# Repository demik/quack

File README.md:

# Quack Mouse Converter   [![Badge License]][License]&nbsp;[![Badge CI]][CI]

A dongle that allows various retro systems to use the `Apple Desktop Bus` as well as `Bluetooth 2+` mice through their `quadrature` mouse ports.

<br>
<br>
<br>

<div align = center>

[![Button Documentation]][Documentation]   
[![Button Firmware]][Firmware]   
[![Button PCB]][PCB]   
[![Button Changelog]][Changelog]

<br>
<br>

</div>

<br>
<br>

## Supported

#### Systems

<kbd>&nbsp;&nbsp;Macintosh 128 / 512 / Plus&nbsp;&nbsp;</kbd> 
<kbd>&nbsp;&nbsp;Apple Lisa&nbsp;&nbsp;</kbd> 
<kbd>&nbsp;&nbsp;Apple IIc&nbsp;&nbsp;</kbd> 
<a href="https://github.com/DosFox1/OSHintosh"><kbd>&nbsp;&nbsp;OSHintosh&nbsp;&nbsp;</kbd></a>

#### Connection Types

<kbd>  Apple Desktop Bus  </kbd> <kbd>  Bluetooth Classic 2+  </kbd>

<br>
<br>

<!----------------------------------------------------------------------------->

[Documentation]: https://github.com/demik/quack/wiki

[Changelog]: ChangeLog.md
[Firmware]: main/README.md
[License]: LICENSE
[PCB]: EDA/ChangeLog.md
[CI]: https://github.com/demik/quack/actions/workflows/idf.yml
[OSHintosh]: https://github.com/DosFox1/OSHintosh

<!-------------------------------[ Badges ]----------------------------------->

[Badge License]: https://img.shields.io/badge/License-Apache_2.0-961b1f?labelColor=D22128
[Badge CI]: https://github.com/demik/quack/actions/workflows/idf.yml/badge.svg?branch=master&event=push

<!-------------------------------[ Buttons ]----------------------------------->

[Button Documentation]: https://img.shields.io/badge/Documentation-0099E5?style=for-the-badge&logoColor=white&logo=BookStack
[Button Changelog]: https://img.shields.io/badge/Changelog-21375A?style=for-the-badge&logoColor=white&logo=AzureArtifacts
[Button Firmware]: https://img.shields.io/badge/Firmware-E5426E?style=for-the-badge&logoColor=white&logo=ROS
[Button PCB]: https://img.shields.io/badge/PCB-007c40?style=for-the-badge&logoColor=white&logo=PowerApps

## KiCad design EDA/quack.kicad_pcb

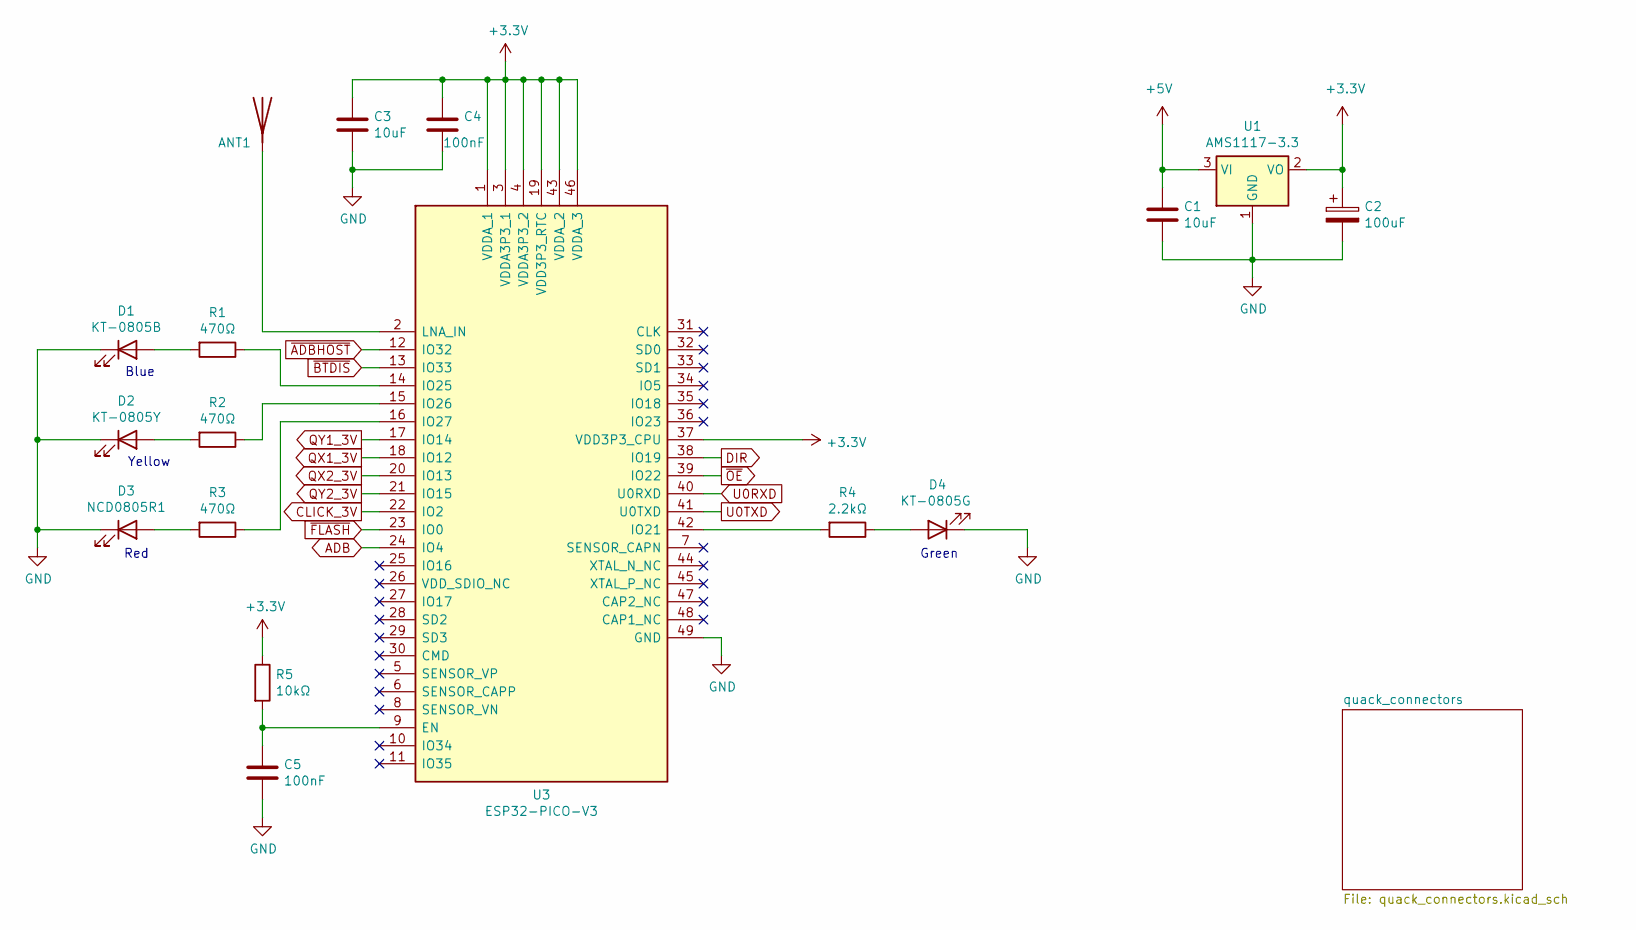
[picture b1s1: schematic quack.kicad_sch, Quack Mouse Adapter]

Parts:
ANT1: Antenna_Shield; Texas_SWRA117D_2.4GHz_Right
C1, C3: 10uF; C_0805_2012Metric
C2: 100uF; CP_EIA-3528-12_Kemet-T
C4, C5: 100nF; C_0805_2012Metric
D1: KT-0805B; LED_0805_2012Metric
D2: KT-0805Y; LED_0805_2012Metric
D3: NCD0805R1; LED_0805_2012Metric
D4: KT-0805G; LED_0805_2012Metric
R1, R2, R3: 470Ω; R_0805_2012Metric
R4: 2.2kΩ; R_0805_2012Metric
R5: 10kΩ; R_0805_2012Metric
U1: AMS1117-3.3; SOT-223-3_TabPin2
U3: ESP32-PICO-V3; QFN-48-1EP_7x7mm_P0.5mm_EP5.3x5.3mm; Mouser Part Number 356-ESP32-PICO-V3

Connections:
+3.3V: C2.1, C3.1, C4.1, R5.1, U1.2 (VO), U3.1 (VDDA_1), U3.3 (VDDA3P3_1), U3.4 (VDDA3P3_2), U3.19 (VDD3P3_RTC), U3.37 (VDD3P3_CPU), U3.43 (VDDA_2), U3.46 (VDDA_3); also elsewhere on the board
+5V: C1.1, U1.3 (VI); also elsewhere on the board
ADB: U3.24 (IO4); also elsewhere on the board
CLICK_3V: U3.22 (IO2); also elsewhere on the board
DIR: U3.38 (IO19); also elsewhere on the board
GND: C1.2, C2.2, C3.2, C4.2, C5.2, D1.1 (K), D2.1 (K), D3.1 (K), D4.1 (K), U1.1 (GND), U3.49 (GND); also elsewhere on the board
unnamed: ANT1.1 (A), U3.2 (LNA_IN)
unnamed: D1.2 (A), R1.2
unnamed: D2.2 (A), R2.2
unnamed: D3.2 (A), R3.2
unnamed: D4.2 (A), R4.1
unnamed: C5.1, R5.2, U3.9 (EN)
unnamed: R4.2, U3.42 (IO21)
unnamed: R1.1, U3.14 (IO25)
unnamed: R2.1, U3.15 (IO26)
unnamed: R3.1, U3.16 (IO27)
QX1_3V: U3.18 (IO12); also elsewhere on the board
QX2_3V: U3.20 (IO13); also elsewhere on the board
QY1_3V: U3.17 (IO14); also elsewhere on the board
QY2_3V: U3.21 (IO15); also elsewhere on the board
U0RXD: U3.40 (U0RXD); also elsewhere on the board
U0TXD: U3.41 (U0TXD); also elsewhere on the board
~ADBHOST: U3.12 (IO32); also elsewhere on the board
~BTDIS: U3.13 (IO33); also elsewhere on the board
~FLASH: U3.23 (IO0); also elsewhere on the board
~OE: U3.39 (IO22); also elsewhere on the board

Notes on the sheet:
Blue
Red
Green
Yellow

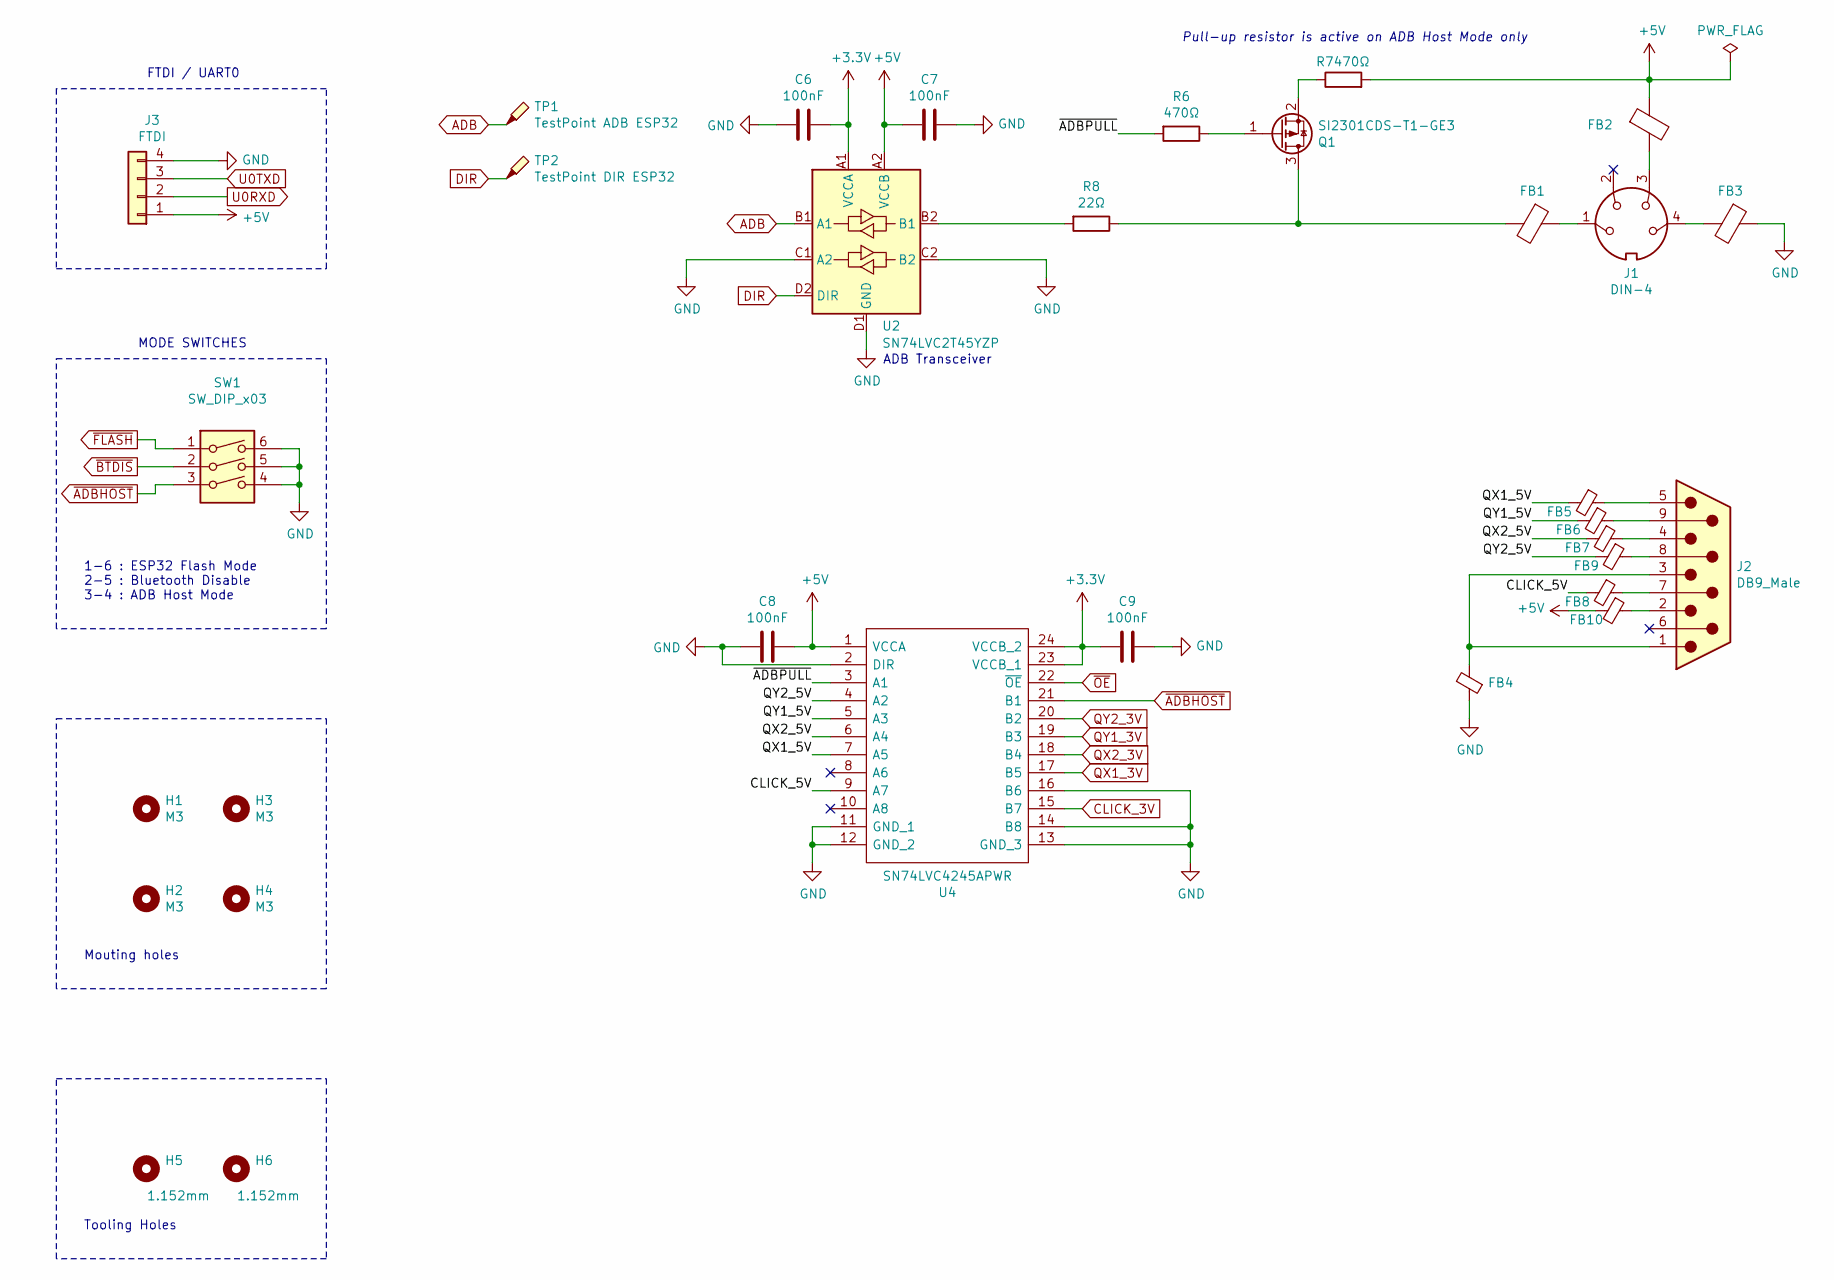
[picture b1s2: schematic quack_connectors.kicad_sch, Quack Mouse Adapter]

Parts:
C6, C7, C8, C9: 100nF; C_0805_2012Metric
FB1, FB2, FB3, FB4, FB5, FB6, FB7, FB8, FB9, FB10: GZ2012D601TF; L_0805_2012Metric
H1, H2, H3, H4: M3; MountingHole_3.2mm_M3_Pad
H5, H6: 1.152mm; MountingHole_1.152mm
J1: DIN-4; 5749181-1
J2: DB9_Male; 23018431
J3: FTDI; PinHeader_1x04_P2.54mm_Vertical
Q1: SI2301CDS-T1-GE3; SOT-23
R6, R7: 470Ω; R_0805_2012Metric
R8: 22Ω; R_0805_2012Metric
SW1: SW_DIP_x03; SW_DIP_SPSTx03_Slide_9.78x9.8mm_W7.62mm_P2.54mm
TP1: TestPoint ADB ESP32; TestPoint_Pad_1.0x1.0mm
TP2: TestPoint DIR ESP32; TestPoint_Pad_1.0x1.0mm
U2: SN74LVC2T45YZP; Texas_DSBGA-8_0.9x1.9mm_Layout2x4_P0.5mm
U4: SN74LVC4245APWR; TSSOP-24_4.4x7.8mm_P0.65mm; Mouser Part Number 595-SN74LVC4245APWR

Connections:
+3.3V: C6.1, C9.2, U2.A1 (VCCA), U4.23 (VCCB_1), U4.24 (VCCB_2); also elsewhere on the board
+5V: C7.2, C8.1, FB2.1, FB10.2, J3.1, R7.2, U2.A2 (VCCB), U4.1 (VCCA); also elsewhere on the board
/quack_connectors/CLICK_5V: FB8.2, U4.9 (A7)
/quack_connectors/QX1_5V: FB5.2, U4.7 (A5)
/quack_connectors/QX2_5V: FB7.2, U4.6 (A4)
/quack_connectors/QY1_5V: FB6.2, U4.5 (A3)
/quack_connectors/QY2_5V: FB9.2, U4.4 (A2)
/quack_connectors/~ADBPULL: R6.2, U4.3 (A1)
ADB: TP1.1, U2.B1 (A1); also elsewhere on the board
CLICK_3V: U4.15 (B7); also elsewhere on the board
DIR: TP2.1, U2.D2 (DIR); also elsewhere on the board
GND: C6.2, C7.1, C8.2, C9.1, FB3.1, FB4.1, J3.4, SW1.4, SW1.5, SW1.6, U2.C1 (A2), U2.C2 (B2), U2.D1 (GND), U4.2 (DIR), U4.11 (GND_1), U4.12 (GND_2), U4.13 (GND_3), U4.14 (B8), U4.16 (B6); also elsewhere on the board
unnamed: FB1.1, J1.1
unnamed: FB2.2, J1.3
unnamed: FB3.2, J1.4
unnamed: FB4.2, J2.1, J2.3
unnamed: FB5.1, J2.5
unnamed: FB6.1, J2.9
unnamed: FB7.1, J2.4
unnamed: FB8.1, J2.7
unnamed: FB9.1, J2.8
unnamed: FB10.1, J2.2
unnamed: FB1.2, Q1.3 (D), R8.1
unnamed: Q1.1 (G), R6.1
unnamed: Q1.2 (S), R7.1
unnamed: R8.2, U2.B2 (B1)
QX1_3V: U4.17 (B5); also elsewhere on the board
QX2_3V: U4.18 (B4); also elsewhere on the board
QY1_3V: U4.19 (B3); also elsewhere on the board
QY2_3V: U4.20 (B2); also elsewhere on the board
U0RXD: J3.2; also elsewhere on the board
U0TXD: J3.3; also elsewhere on the board
~ADBHOST: SW1.3, U4.21 (B1); also elsewhere on the board
~BTDIS: SW1.2; also elsewhere on the board
~FLASH: SW1.1; also elsewhere on the board
~OE: U4.22 (~OE); also elsewhere on the board

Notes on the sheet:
1-6 : ESP32 Flash Mode 2-5 : Bluetooth Disable 3-4 : ADB Host Mode
Mouting holes
MODE SWITCHES
ADB Transceiver
Pull-up resistor is active on ADB Host Mode only
Tooling Holes
FTDI / UART0

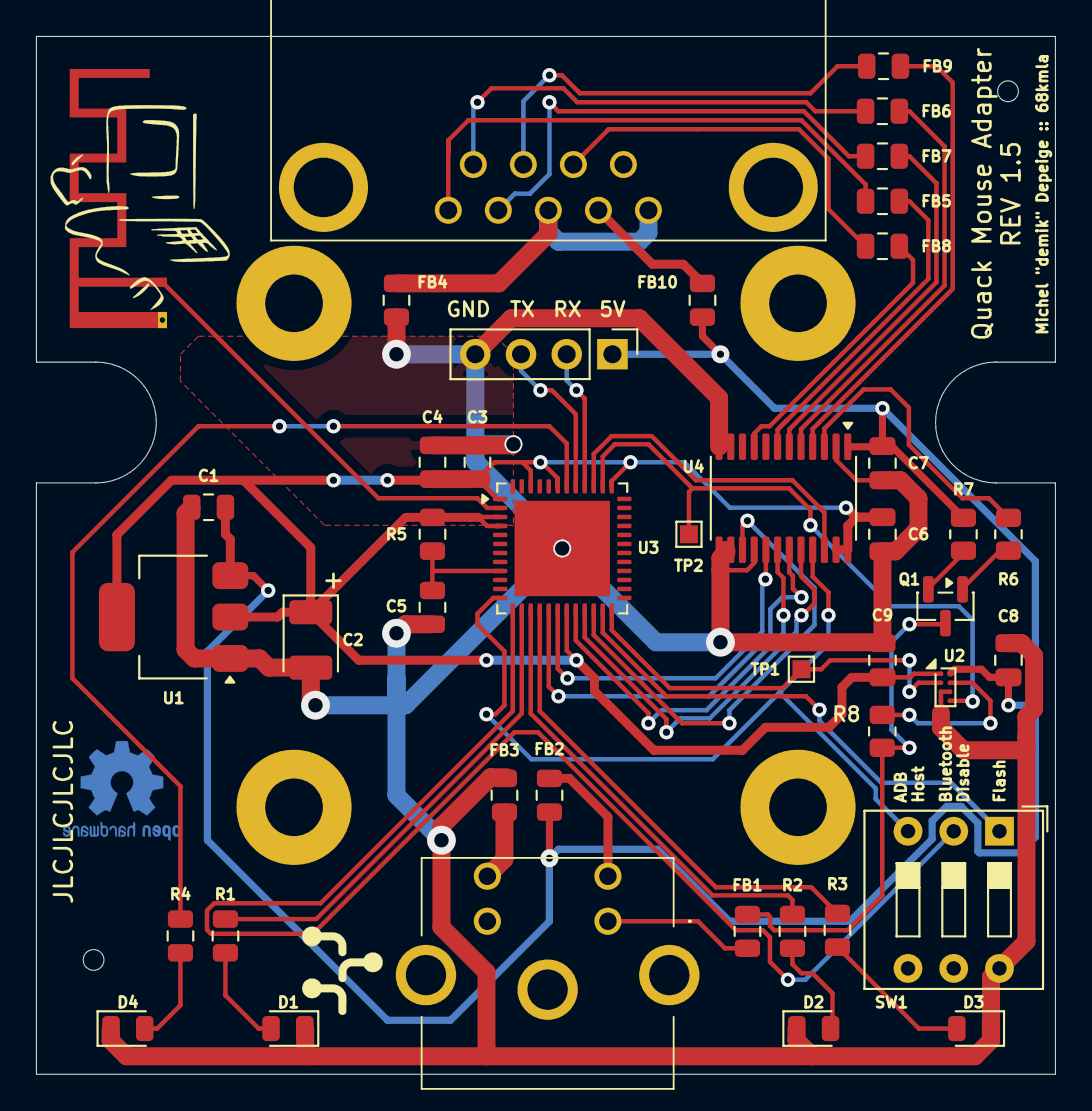
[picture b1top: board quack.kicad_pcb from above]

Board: 2 copper layers, 56.6 x 57.7 mm, 49 parts (0 on the bottom side), 46 nets.

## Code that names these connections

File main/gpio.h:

/*
 *  gpio.h
 *  quack
 *
 *  Created by Michel DEPEIGE on 13/09/2020.
 *  Copyright (c) 2020 Michel DEPEIGE.
 *
 * This program is free software; you can redistribute it and/or modify
 * it under the terms of the Apache License, Version 2.0 (the "License");
 * You may obtain a copy of the License at:
 *
 *      http://www.apache.org/licenses/LICENSE-2.0
 *
 * Unless required by applicable law or agreed to in writing, software
 * distributed under the License is distributed on an "AS IS" BASIS,
 * WITHOUT WARRANTIES OR CONDITIONS OF ANY KIND, either express or implied.
 * See the License for the specific language governing permissions and
 * limitations under the License.
 *
 */

#ifndef GPIO_H
#define GPIO_H

/* prototypes */
void	gpio_init(void);
void    gpio_transceiver_disable(void);
void    gpio_transceiver_enable(void);

/* GPIO pins definitions
 *
 * pin layout is compatible with ESP32-CAM module for prototyping
 * LEDs aren't avaible on ESP32-CAM but DEBUG LED (Camera connector)
 *
 * on ESP32-CAM the following pins are already used:
 * - CSI_MCLK (GPIO0)
 * - U0TXD (GPIO1)
 * - U0TXD (GPIO3)
 * - FLASH (GPIO4)
 *
 * on ESP32-PICO-D4, the following pins are used for connecting the
 * embedded flash:
 * - CLK (GPIO6)
 * - SD0 (GPIO7)
 * - SD1 (GPIO8)
 * - CMD (GPIO11)
 * - GPIO16
 * - GPIO17
 */

#define GPIO_ADB		4
#define GPIO_CLICK		2
#define GPIO_QX1		12
#define GPIO_QX2		13
#define GPIO_QY1		14
#define GPIO_QY2		15

#define GPIO_DIR		19
#define GPIO_OE		22
#define GPIO_ADBSRC		32
#define GPIO_BTOFF		33

#define GPIO_GREENLED	21
#define GPIO_BLUELED	25
#define GPIO_YELLOWLED	26
#define GPIO_REDLED		27

#define GPIO_NULL		5

#endif

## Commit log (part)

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2020-09-15 added pin usage text + logos
2020-09-15 moved libs to subfolder
2020-09-25 added beads to reduce EMI
2020-12-14 upgraded toolkit to v4.2@20201214
2020-12-14 starting to work with LEDs
2020-12-16 added led management tasks
2020-12-18 some bluetooth code cleaning
2020-12-18 board revision 1.1
2020-12-21 added missing GPIO + disable Bluetooth if /BTOFF
2020-12-30 bluetooth tinkering
2020-12-30 revision 1.2: move ADB socket 2mm out
2020-12-31 fixed indenting
2021-01-08 try to init adb
2021-01-08 Board revision 1.2
2021-01-11 init ADB devices correctly
2021-03-21 start of ADB stack: send reset command on startup
2021-03-22 more adb coding + ESP-IDF update
2021-03-23 added missing adb.h
2021-03-24 Update ChangeLog.md
    Formating fixes
2021-03-24 adb clode cleaning
2021-04-01 more ADB hakinck
2021-04-03 replaced RXS0108EPWR by 74LVC2T45 + 74LVC4245
2021-04-03 mix fixes: silk, routing, 3D shapes
2021-04-04 fixed quad transceiver footprint + reduce led brightness
2021-04-05 PCB version 1.3
2021-04-05 fixed some SMT positions for pick and place
2021-04-17 added mounting holes to schematic
2021-04-18 Pull request #6385 from ESP-IDF
2021-04-18 tuned sdkconfig to get Bluetooth working again
2021-04-20 Quadrature and Bluetooth tinkering
2021-05-03 ADB Parsing 90% done, quadrature output issues
2021-05-07 SDK v4.2.1 update
2021-05-07 Changed pin code to 0000
2021-05-08 ADB code cleaning
2021-05-08 increase tick rate to 250Hz
2021-05-08 fixed timings and code cleaning
2021-05-08 Quadratures fixes: x movement, pullups, timings
2021-05-09 added ADB Mouse HotPlug management
2021-05-09 bluetooth -> quadrature 90% working. Need to tweak timings
2021-05-31 fixed ADB Sync timing
2021-06-08 PCB v1.4
2021-06-10 License project with Apache version 2.0
2021-08-05 increase RMT buffer and stability on data rx errors
2021-08-05 code compilation optimizations
2021-08-09 hardened the ADB Host to spurious transmissions a little bit
2021-08-09 code cleaning
2021-08-11 renamed ADB mouse mode to ADB idle mode
2021-08-15 fixed R1 and R4 values
2021-08-16 rotated U2 by 90°
2021-08-16 moved LEDs to LEDC module, fade slow blink, and move LEDs to CPU 1
2021-08-17 commited SDK 4.2 patch
2021-08-18 rename Bluetooth Host function as blue_h_*
2021-08-18 Licenses update + basic ADB to Bluetooth
2021-08-20 switched auth to ESP_IO_CAP_OUT
2021-08-20 do not send mouse updated to BLE if not connected
2021-08-21 code cleaning + freeing memory after init
2021-08-21 move quadrature tasks from notification to queue
2021-08-22 pin LED and ADB to core 1 again
2021-08-22 Firmware ChangeLog created
2021-08-23 Updating main README.md
2021-08-24 Added Wiki link
2021-08-24 Documentation for main subfolder
2021-08-26 Fixed wording
2021-09-08 Datasheet for ADB Socket
2021-09-19 compile against SDK v4.2.2
2021-09-20 fixed BT LED state when using multiple mouses
2021-10-12 added PCB image
2021-10-12 Added photo on README.md
2021-10-30 added support for MicroSpeed MacTRAC 2.0
2021-10-30 fixed BT LED state in case some mouse is reconnecting while the quack is scanning
2021-11-20 Added support for Apple Lisa
2021-12-02 provides some slight acceleration and desceleration on bluetooth mouses
2021-12-22 fix typo
2021-12-23 Reworked README
2021-12-23 Fixed Names
2022-01-04 added back panel using a PCB
2022-01-04 cleaning
2022-04-03 Upgraded SDK to v4.2.3
2022-07-05 Cut Out Preview
2022-07-05 Formatted README
2022-07-05 Adjusted Spacing
2022-07-05 Updated Support Section
2022-08-02 Adjusted Badge Style
2022-08-03 Added Bigger Preview
2023-12-28 Upgraded SDK to v5.1.2
2023-12-28 Updated ChangeLog to 1.4.5
2024-06-03 early work to restore ADB to bluetooth functionality
2024-06-04 added support for Kensington ADB Devices
2024-06-05 fix ADB start and stop bit timings
2024-06-06 Upgraded SDK to v5.2.2
2024-06-07 added complex PCB front panel
2024-06-08 New FR-4 based front panel with shine-through LEDs
2024-06-17 sync register probing to scheduling
2024-06-17 added new FR-4 front panel
2024-06-18 added half click feature (on BT right click)
2024-06-25 added support for MacAlly Joystick (thanks tashtari@68kmla !)
2024-07-02 added Apple IIc compatibility
2024-08-10 esp_hidh_dev_open() doesn't give a toss about BLE address types in our case
2024-08-14 added wii remote support (buttons)
2024-08-15 updated README for v1.4.8
2024-08-22 added basic support for some PDP Rock Candy Wiimotes
2024-08-29 added resources for esp_8_bit build
2024-08-29 added README for Quack X esp_8_bit
2024-08-29 fixed typo
2024-09-25 Back panel update: Apple IIc
2024-09-25 modified clearance
2025-02-10 upgraded Changelog for v1.4.9
2025-03-03 Create idf.yml
    gibve a try at espressif/esp-idf-ci-action
2025-03-03 only start github actions when push to master/main
2025-03-03 ESP-IDF v5.4 code modifications
2025-03-03 fix GHA path
2025-03-03 5.4.0 doc update
2025-03-03 added Mighty Mouse driver
2025-03-03 Update README.md
    added CI badge + minot fixes
2025-03-07 upgraded Changelog for v1.4.10
2025-03-08 added name to action idf.yml
2025-03-18 added flash switch watchdog
2025-03-20 Revert "added flash switch watchdog"
    This reverts commit 9152b953aa4b516238fd8f009775ccb52d42a4be because you can't enter bootloader from esp_restart() on ESP32
2025-06-29 1.4.11 update
2025-06-29 provisioned m5769 header as documentation
2025-12-14 PCB v1.5
2025-12-27 upgraded SDK to v5.5.2 + new low level ADB receiver driver
2025-12-30 pre v1.5 code cleaning and documentation
2026-02-19 upgraded SDK to v5.5.3
2026-02-25 misc Bluetooth stability improvements with ESP-IDF v5.5
2026-03-21 esp_hid_gap: log cleaning
2026-04-18 upgraded SDK to v5.5.4
2026-04-18 reverted PCB revision to 1.5
2026-05-01 EDA lib: updated Mini DIN 4 connector
2026-05-01 bump emerald LED from 1.5kΩ to 2.2kΩ
2026-05-03 moved all logos footprints to Quack_logo.pretty
2026-06-22 Added OSHintosh compatibility
    also removed unsupported ADB to BLE mode
